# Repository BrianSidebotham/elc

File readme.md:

# Electronic Load Controller

This project is subject to the [CERN Open Hardware Licence](http://www.ohwr.org/attachments/2388/cern_ohl_v_1_2.txt)

Electronic Load Controller Design is available [here](http://ludens.cl/Electron/picelc/picelc.html).

This repository is a direct implementation of the ludens.cl ELC circuit.

The Schematic and Printed Circuit Board have been produced in
[KiCad](http://kicad.org). The Printed circuit board has been routed
single-layer so it may be possible to etch your own easily enough. Otherwise it
can be made very cheaply. There's plenty of improvements that can be made to
the design, and there's plenty of optimisations for the PCB layout too if you
fancy changing things up.

To use this Load Controller you'll need a way to program the PIC microcontroller
and you'll have to use the [code available on the lidens.cl website](http://ludens.cl/Electron/picelc/picelc.bas).
Perhaps they can make a binary available for anyone to use without them having
to use the PIC basic compiler.

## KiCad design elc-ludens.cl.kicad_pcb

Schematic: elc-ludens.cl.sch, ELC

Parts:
C1: 220pF; Farnell 9411755
C2: 33uF; Farnell 1902890
C3: 3300uF; Farnell 1902894
C4: 10uF; Farnell 1236657
C5: 0.1uF; Farnell 2309020
C6, C7: 22pF; Farnell 1457695
D1, D2, D5, D6: 1N4004; Farnell 2317685
D3, D4: 1N4148; Farnell 2336736
D7: GREEN; Farnell 2217954
P1, P2, P3: CONN_2; Farnell 1172817
P4: CONN_8; Farnell 1142163
P5, P6, P7: CONN_1
Q1, Q2, Q3, Q4, Q5, Q6, Q7, Q8: BC337; TO92-EBC
R1: 4k7; Farnell 2329534
R2, R3, R4, R5, R6, R11, R12, R13, R14: 2k2; Farnell 2329508
R7, R8, R9, R10, R15, R16, R17, R18: 47R; Farnell 2329533
R19: 330R; Farnell 2329514
R20: 2k2
U1: 7805; Farnell 1564483
U2: PIC16F628; Farnell 9760423
X1: 4MHz; Farnell 1842254

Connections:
/COMP1: C1.1, D3.2 (K), D4.1 (A), R1.2, U2.18 (RA1/AN1)
/COMP2: C1.2, C2.1, D3.1 (A), D4.2 (K), P3.2 (PM), R2.1, R20.2, U2.1 (RA2/AN2/VREF)
/DRV1: R3.1, U2.6 (RB0/INT)
/DRV2: R4.1, U2.7 (RB1/RX/DT)
/DRV3: R5.1, U2.8 (RB2/TX/CK)
/DRV4: R6.1, U2.9 (RB3/CCP1)
/DRV5: R11.1, U2.17 (RA0/AN0)
/DRV6: R12.1, U2.11 (RB5)
/DRV7: R13.1, U2.12 (RB6/T1OSC0/T1CKI/PGC)
/DRV8: R14.1, U2.13 (RB7/T1OSI/PGD)
/GATE1: P4.1, R7.2
/GATE2: P4.2, R8.2
/GATE3: P4.3, R9.2
/GATE4: P4.4, R10.2
/GATE5: P4.5, R15.2
/GATE6: P4.6, R16.2
/GATE7: P4.7, R17.2
/GATE8: P4.8, R18.2
GND: C2.2, C3.2, C4.2, C5.2, C6.2, C7.2, D2.1 (A), D6.1 (A), D7.2 (K), Q1.E, Q2.E, Q3.E, Q4.E, Q5.E, Q6.E, Q7.E, Q8.E, R2.2, U1.GND, U2.5 (VSS), U2.10 (RB4/PGM)
unnamed: Q5.C, R15.1
unnamed: Q6.B, R12.2
unnamed: Q5.B, R11.2
unnamed: Q7.B, R13.2
unnamed: Q7.C, R17.1
unnamed: Q6.C, R16.1
unnamed: Q2.B, R4.2
unnamed: Q2.C, R8.1
unnamed: Q1.C, R7.1
unnamed: Q4.B, R6.2
unnamed: Q4.C, R10.1
unnamed: Q3.B, R5.2
unnamed: Q3.C, R9.1
unnamed: Q1.B, R3.2
unnamed: Q8.C, R18.1
unnamed: Q8.B, R14.2
unnamed: P3.1, R1.1
unnamed: R19.1, U2.2 (RA3/AN3/CMP1)
unnamed: D5.1 (A), D6.2 (K), P2.2 (PM)
unnamed: D1.1 (A), D2.2 (K), P2.1
unnamed: C3.1, D1.2 (K), D5.2 (K), U1.VI
unnamed: C7.1, U2.15 (OSC2), X1.1
unnamed: C6.1, U2.16 (OSC1), X1.2
unnamed: D7.1 (A), R19.2
VDD: C4.1, C5.1, P1.2 (PM), R20.1, U1.VO, U2.4 (MCLR), U2.14 (VDD)

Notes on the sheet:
USE PDIP PACKAGE
MECHANICAL FIXINGS

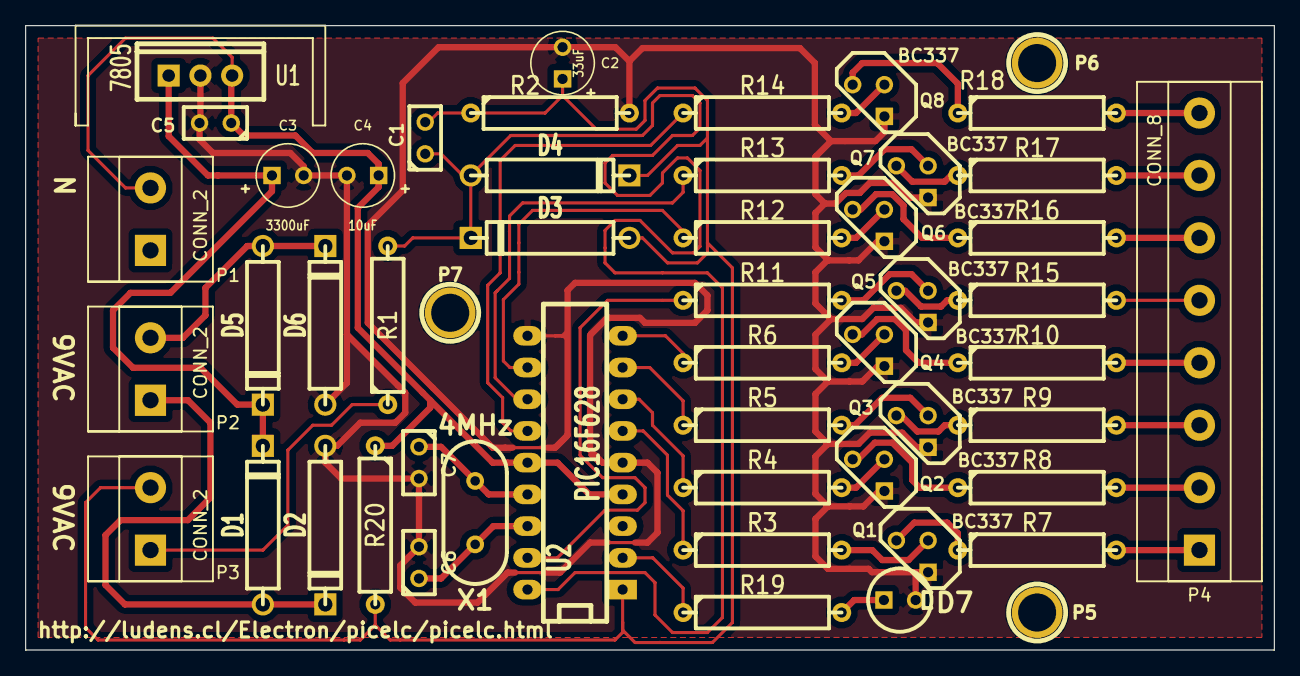
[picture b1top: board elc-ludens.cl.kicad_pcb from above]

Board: 2 copper layers, 100.0 x 50.0 mm, 52 parts (0 on the bottom side), 44 nets.

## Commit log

2014-01-03 First revision bought into version control
    Electronic Load Controller Project
2014-01-03 Tidy PCB and add Fixing Holes
    Must use nylon/plastic hardware to use the fixing holes
2014-01-03 Add the production readme.md
2014-01-06 Add missing resistor
2014-01-17 Layout fix BC337 pinout + Add resistor
2014-01-17 * Remove backup files
2014-01-30 Finalise PCB Design and produce production gerbers
2021-11-08 Update readme.md
    https://forum.kicad.info/t/warning-avoid-all-links-to-kicad-pcb-org-use-kicad-org/31521
